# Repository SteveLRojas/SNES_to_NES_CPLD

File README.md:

# SNES_to_NES_CPLD
SNES_to_NES project using a CPLD instead of a MCU.

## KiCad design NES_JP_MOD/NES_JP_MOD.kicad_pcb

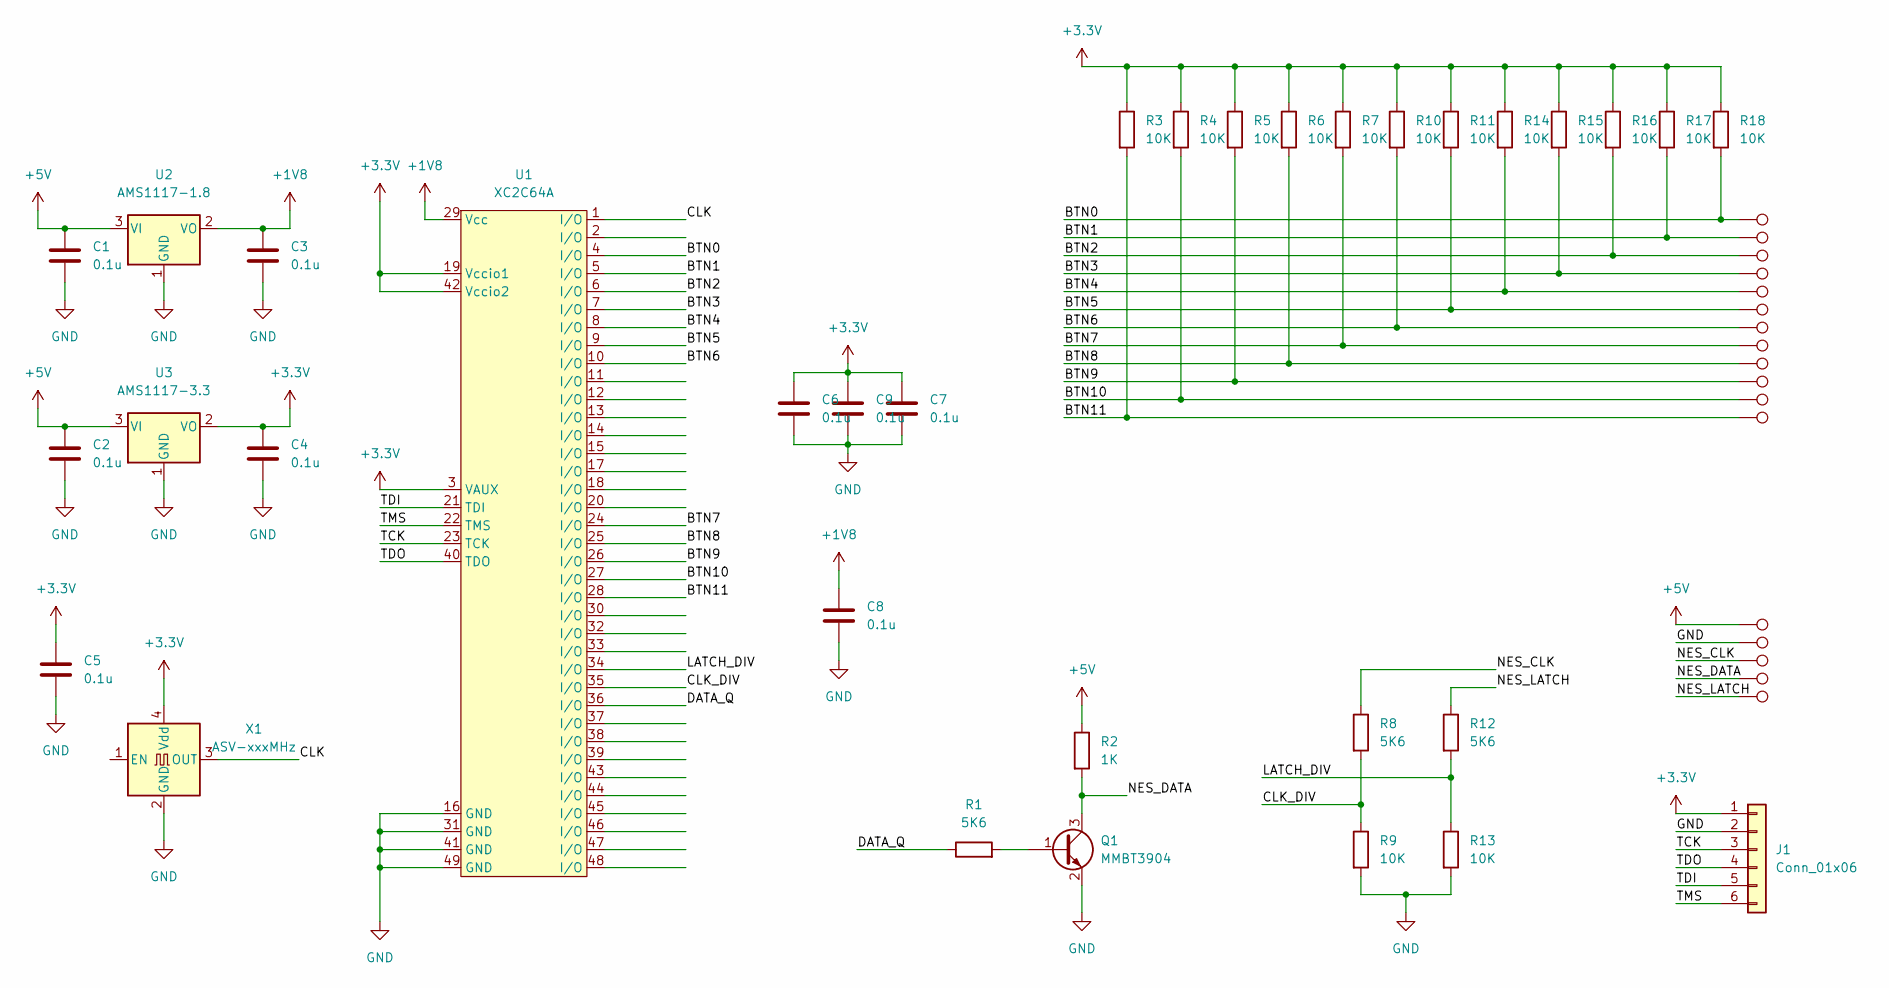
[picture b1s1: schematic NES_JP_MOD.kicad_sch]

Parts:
C1, C2, C3, C4, C5, C6, C7, C8, C9: 0.1u; C_0805_2012Metric
J1: Conn_01x06; PinHeader_1x06_P2.54mm_Vertical
Q1: MMBT3904; SOT-23
R1, R8, R12: 5K6; R_0805_2012Metric
R2: 1K; R_0805_2012Metric
R3, R4, R5, R6, R7, R9, R10, R11, R13, R14, R15, R16, R17, R18: 10K; R_0805_2012Metric
TP1, TP2, TP3, TP4, TP5, TP6, TP7, TP8, TP9, TP10, TP11, TP12, TP13, TP14, TP15, TP16, TP17: TestPoint; TestPoint_Pad_2.0x2.0mm
U1: XC2C64A; QFN-48-1EP_7x7mm_P0.5mm_EP5.15x5.15mm
U2: AMS1117-1.8; SOT-223-3_TabPin2
U3: AMS1117-3.3; SOT-223-3_TabPin2
X1: ASV-xxxMHz; Oscillator_SMD_Abracon_ASV-4Pin_7.0x5.1mm

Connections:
+1V8: C3.1, C8.1, U1.29 (Vcc), U2.2 (VO)
+3V3: C4.1, C5.1, C6.1, C7.1, C9.1, J1.1, R3.1, R4.1, R5.1, R6.1, R7.1, R10.1, R11.1, R14.1, R15.1, R16.1, R17.1, R18.1, U1.3 (VAUX), U1.19 (Vccio1), U1.42 (Vccio2), U3.2 (VO), X1.4 (Vdd)
+5V: C1.1, C2.1, R2.1, TP16.1, U2.3 (VI), U3.3 (VI)
/BTN0: R18.2, TP2.1, U1.4 (I/O)
/BTN1: R17.2, TP3.1, U1.5 (I/O)
/BTN2: R16.2, TP4.1, U1.6 (I/O)
/BTN3: R15.2, TP5.1, U1.7 (I/O)
/BTN4: R14.2, TP6.1, U1.8 (I/O)
/BTN5: R11.2, TP7.1, U1.9 (I/O)
/BTN6: R10.2, TP8.1, U1.10 (I/O)
/BTN7: R7.2, TP9.1, U1.24 (I/O)
/BTN8: R6.2, TP10.1, U1.25 (I/O)
/BTN9: R5.2, TP11.1, U1.26 (I/O)
/BTN10: R4.2, TP12.1, U1.27 (I/O)
/BTN11: R3.2, TP13.1, U1.28 (I/O)
/CLK: U1.1 (I/O), X1.3 (OUT)
/CLK_DIV: R8.2, R9.1, U1.35 (I/O)
/DATA_Q: R1.1, U1.36 (I/O)
/LATCH_DIV: R12.2, R13.1, U1.34 (I/O)
/NES_CLK: R8.1, TP14.1
/NES_DATA: Q1.3 (C), R2.2, TP1.1
/NES_LATCH: R12.1, TP15.1
/TCK: J1.3, U1.23 (TCK)
/TDI: J1.5, U1.21 (TDI)
/TDO: J1.4, U1.40 (TDO)
/TMS: J1.6, U1.22 (TMS)
GND: C1.2, C2.2, C3.2, C4.2, C5.2, C6.2, C7.2, C8.2, C9.2, J1.2, Q1.2 (E), R9.2, R13.2, TP17.1, U1.16 (GND), U1.31 (GND), U1.41 (GND), U1.49 (GND), U2.1 (GND), U3.1 (GND), X1.2 (GND)
unnamed: Q1.1 (B), R1.2

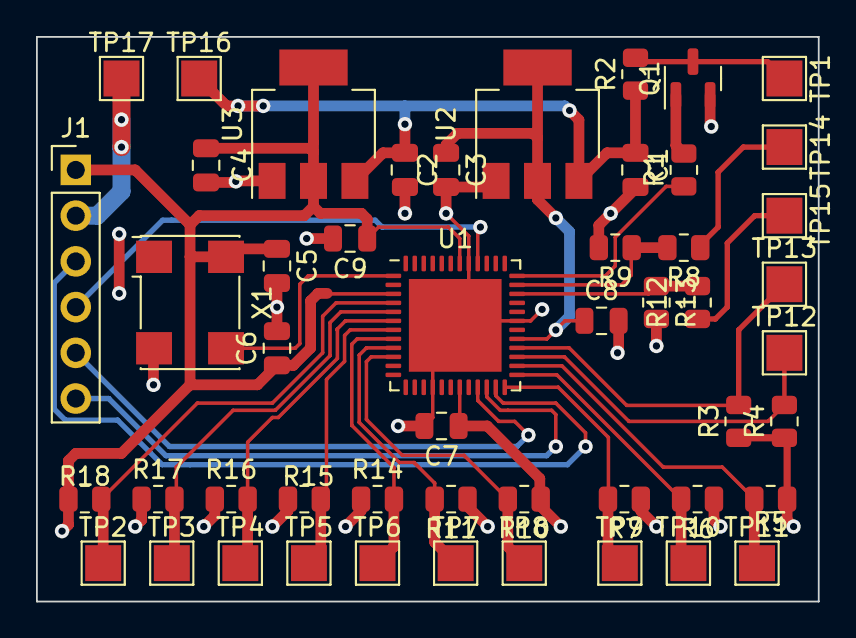
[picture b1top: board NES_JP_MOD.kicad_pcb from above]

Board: 2 copper layers, 43.4 x 31.4 mm, 50 parts (0 on the bottom side), 28 nets.

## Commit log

2023-04-27 Added board files
2023-04-30 Created PCB
2023-05-04 Added ISE project files
2023-06-04 Fixed wrong resistor value
2023-06-15 Fixed comment on button order
